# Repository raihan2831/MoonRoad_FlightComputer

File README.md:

# MoonRoad – F-Class Thrust Vector Control (TVC) Rocket

## 🚀 Overview
**MoonRoad** is an ambitious student-led rocketry project focused on developing an F-class Thrust Vector Control (TVC) rocket. Grounded in the core mission of **VITAL**, the project aims to pioneer reusable vertical take-off and landing (VTVL) rocket systems. 

Through iterative flight testing, precise mathematical modeling, and advanced navigation control, MoonRoad pushes the boundaries of student-engineered aerospace technology.

---

## 🌍 Mission & Vision

### 1. Technical Focus
* **Vertical Take-off & Landing (VTVL):** Designing systems capable of multiple take-offs and landings using rocket motors to refine flight hardware and control loops.
* **Thrust Vector Control & Navigation:** Developing robust dynamic models, state-space equations, and cascade PID control algorithms to manage real-time stabilization and trajectory tracking.
* **Modular Avionics Architecture:** Integrating custom-built Power Distribution Boards (PDBs), high-precision flight computers, high-voltage servos (BMS-A10H), and onboard sensor suites (IMU, barometer, LoRa telemetry).

### 2. Social & Environmental Focus (Sustainability)
* **Reusability over Disposable Hardware:** Challenging the traditional single-use paradigm of model and amateur rocketry to promote sustainable engineering practices.
* **Space Debris Mitigation:** Addressing the critical global challenge of orbital debris and dead satellites that endanger future human spaceflight and near-Earth operations.
* **Interplanetary Readiness:** Aligning with the sustainable technologies required for future long-duration exploration and landing missions on Mars.

---

## 📂 Repository Structure

- **`Power Delivery Board/`** – KiCad schematics, PCB layouts, and component BOMs for the custom power distribution and management system.
- **`Flight Computer PCB/`** – KiCad project files and gerbers for the main flight computer and sensor integration board.
- **`Firmware/`** – Embedded C/C++ firmware (PlatformIO) running on microcontrollers for sensor fusion, telemetry, and actuator control.
- **`Simulation Control/`** – MATLAB and Simulink models implementing state-space representations and cascade PID tuning for the TVC testbench.
- **`telemetry Analysis/`** – Python scripts (NumPy, Matplotlib) for post-flight data processing, sensor logging analysis, and trajectory evaluation.

---

## 🤝 Contributing & Teamwork
MoonRoad brings together diverse engineering disciplines—spanning embedded systems, PCB design, control theory, and mechanical packaging. Whether you are working on hardware integration or flight code, every subsystem is built with flight-readiness and reusability in mind.

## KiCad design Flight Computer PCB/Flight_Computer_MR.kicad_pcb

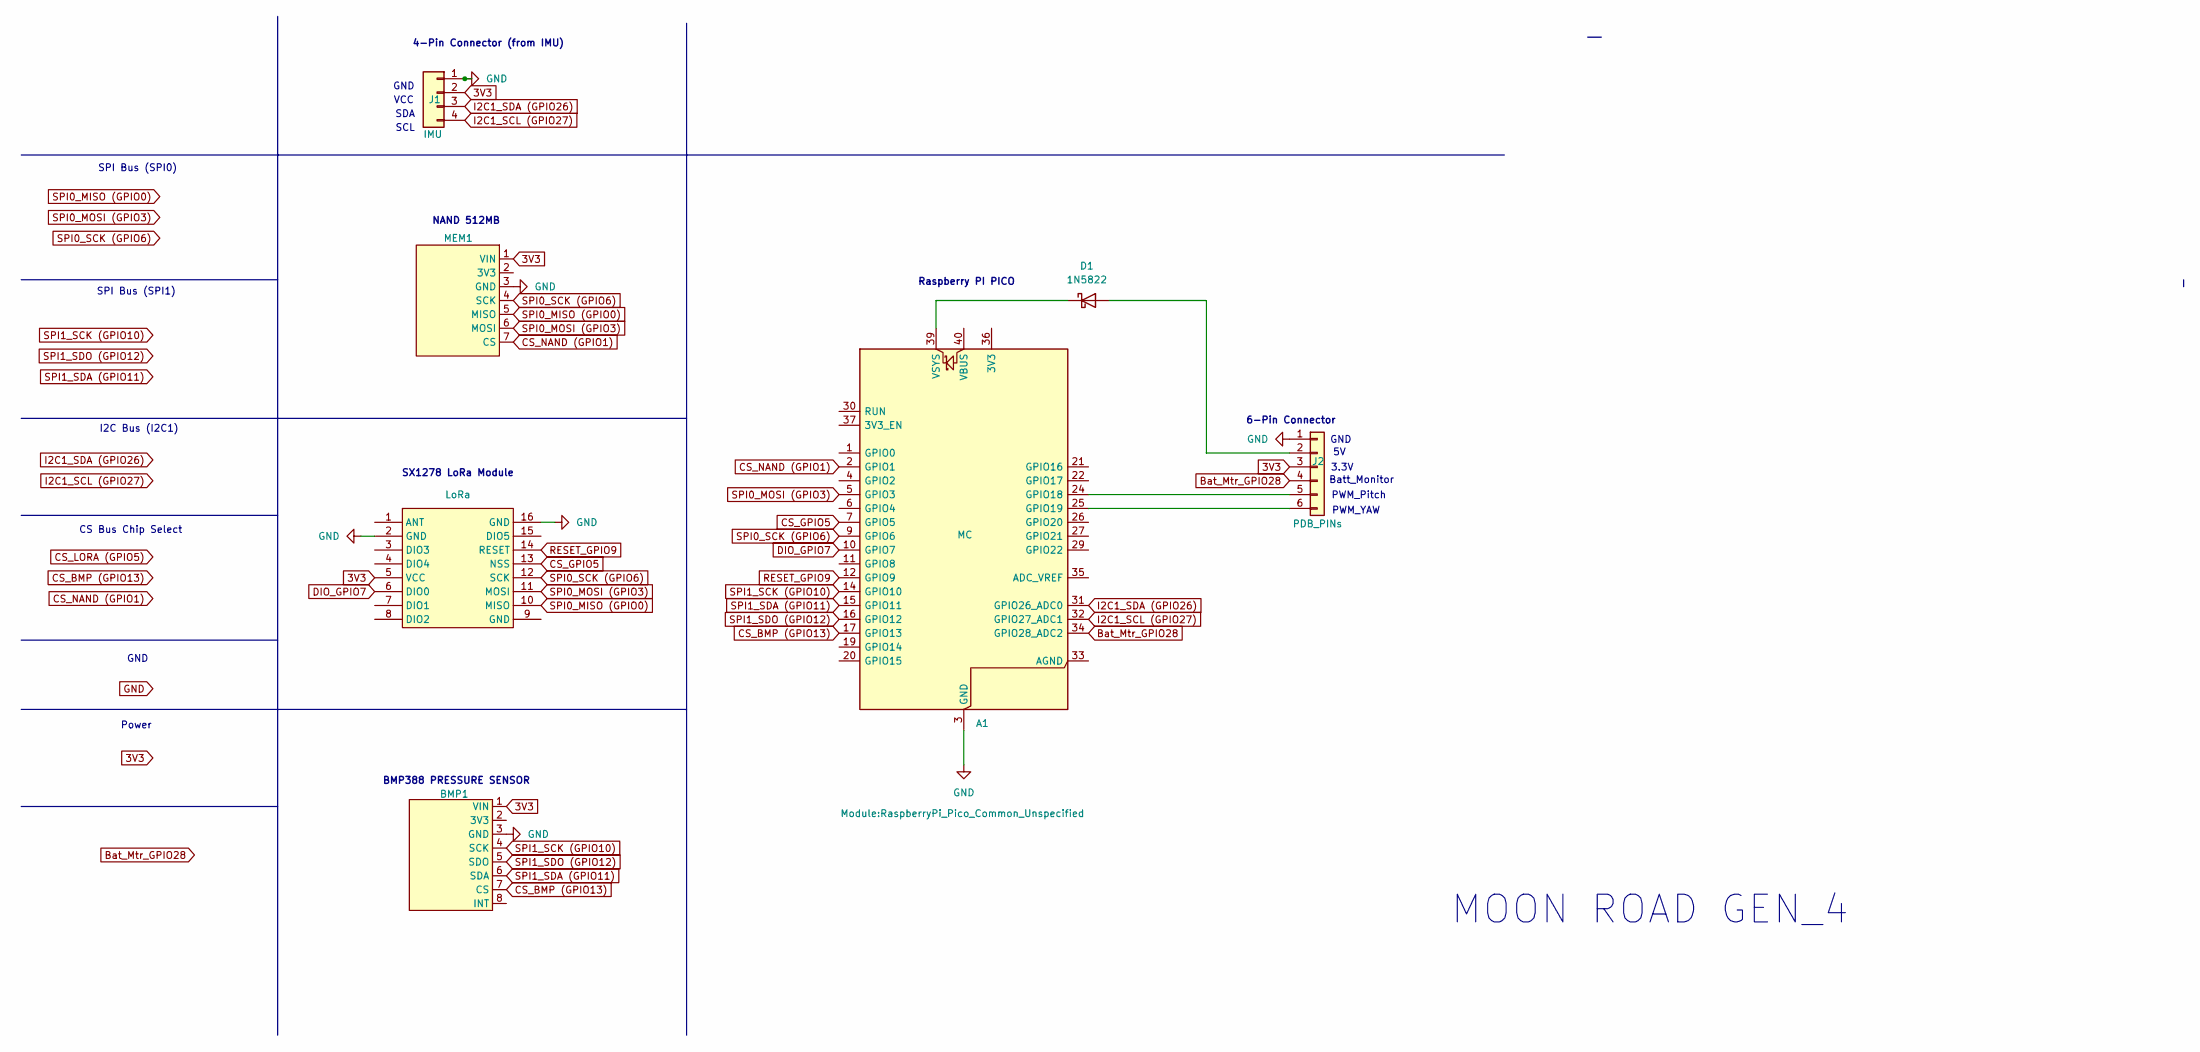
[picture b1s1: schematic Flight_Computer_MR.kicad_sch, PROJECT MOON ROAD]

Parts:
A1: MC; RaspberryPi_Pico_Common_Unspecified
BMP1: PinHeader_1x08_P2.54mm_Vertical
D1: 1N5822; D_DO-201AD_P15.24mm_Horizontal
J1: IMU; NS-Tech_Grove_1x04_P2mm_Vertical
J2: PDB_PINs; PinHeader_1x06_P2.54mm_Vertical
MEM1: PinHeader_1x07_P2.54mm_Vertical
RFS1: LoRa; RFSTX1278

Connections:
3V3: BMP1.1 (VIN), J1.2 (VCC), J2.3 (3V3), MEM1.1 (VIN), RFS1.5 (VCC)
Bat_Mtr_GPIO28: A1.34 (GPIO28_ADC2), J2.4 (Batt_Monitor)
CS_BMP (GPIO13): A1.17 (GPIO13), BMP1.7 (CS)
CS_GPIO5: A1.7 (GPIO5), RFS1.13 (NSS)
CS_NAND (GPIO1): A1.2 (GPIO1), MEM1.7 (CS)
DIO_GPIO7: A1.10 (GPIO7), RFS1.6 (DIO0)
GND: A1.3 (GND), A1.8 (GND), A1.13 (GND), A1.18 (GND), A1.23 (GND), A1.28 (GND), A1.38 (GND), BMP1.3 (GND), J1.1 (GND), J2.1 (GND), MEM1.3 (GND), RFS1.2 (GND), RFS1.16 (GND)
I2C1_SCL (GPIO27): A1.32 (GPIO27_ADC1), J1.4 (SCL)
I2C1_SDA (GPIO26): A1.31 (GPIO26_ADC0), J1.3 (SDA)
unnamed: A1.24 (GPIO18), J2.5 (PWM_Pitch)
unnamed: A1.25 (GPIO19), J2.6 (PWM_Yaw)
unnamed: A1.39 (VSYS), D1.1 (K)
unnamed: D1.2 (A), J2.2 (5V)
RESET_GPIO9: A1.12 (GPIO9), RFS1.14 (RESET)
SPI0_MISO (GPIO0): MEM1.5 (MISO), RFS1.10 (MISO)
SPI0_MOSI (GPIO3): A1.5 (GPIO3), MEM1.6 (MOSI), RFS1.11 (MOSI)
SPI0_SCK (GPIO6): A1.9 (GPIO6), MEM1.4 (SCK), RFS1.12 (SCK)
SPI1_SCK (GPIO10): A1.14 (GPIO10), BMP1.4 (SCK)
SPI1_SDA (GPIO11): A1.15 (GPIO11), BMP1.6 (SDA)
SPI1_SDO (GPIO12): A1.16 (GPIO12), BMP1.5 (SDO)

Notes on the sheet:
NAND 512MB
SX1278 LoRa Module
GND
SPI Bus (SPI0)
SCL
3.3V
6-Pin Connector
PWM_Pitch
SDA
Batt_Monitor
BMP388 PRESSURE SENSOR
Power
SPI Bus (SPI1)
CS Bus Chip Select
PWM_YAW
MOON ROAD GEN_4
I2C Bus (I2C1)
VCC
4-Pin Connector (from IMU)
Raspberry PI PICO
GND

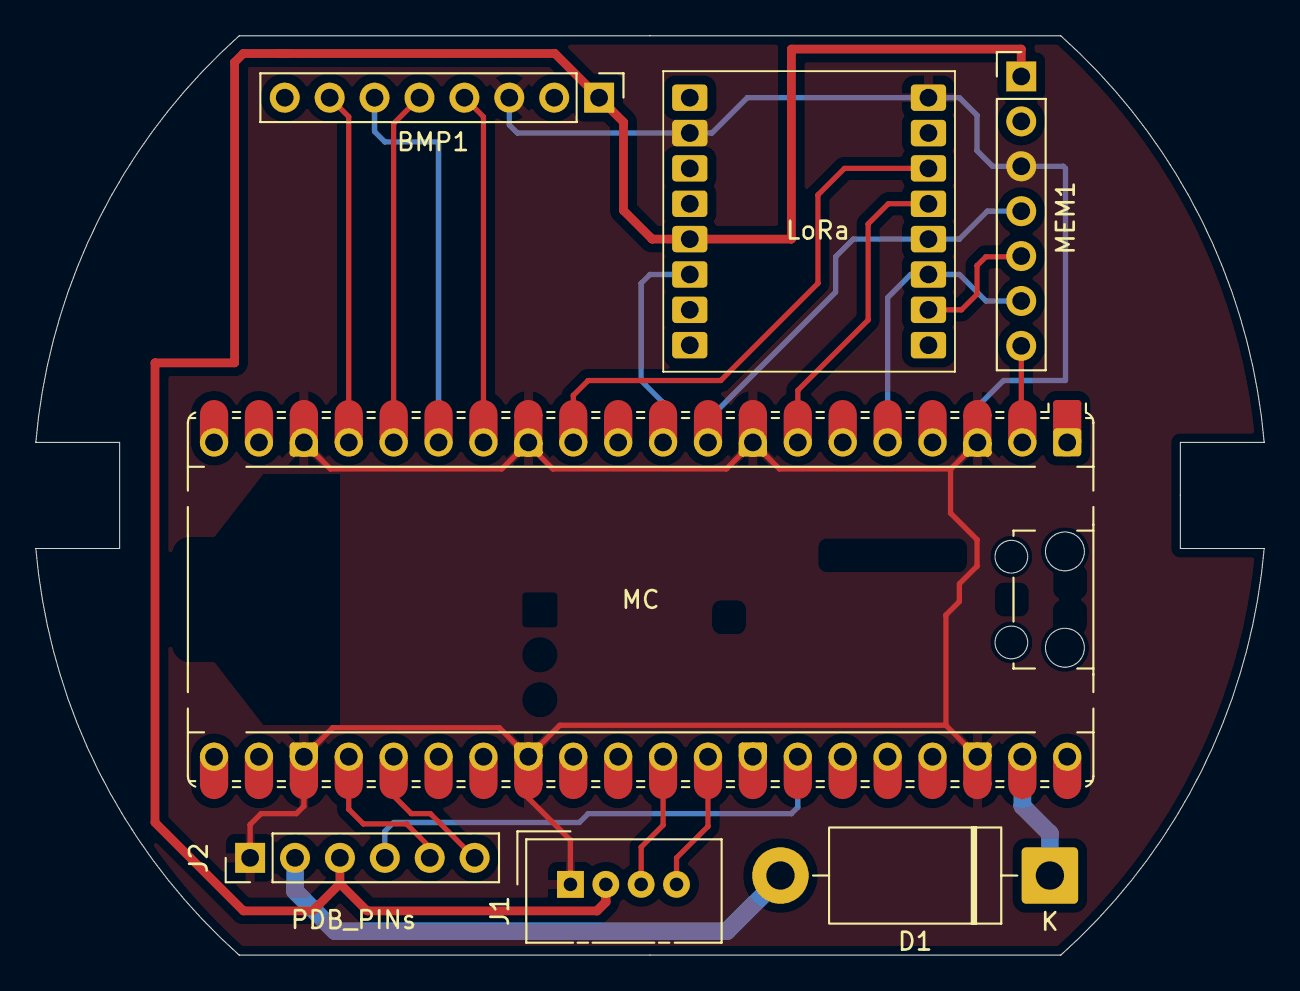
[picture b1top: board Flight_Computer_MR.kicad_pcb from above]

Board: 2 copper layers, 69.5 x 52.0 mm, 7 parts (0 on the bottom side), 20 nets.

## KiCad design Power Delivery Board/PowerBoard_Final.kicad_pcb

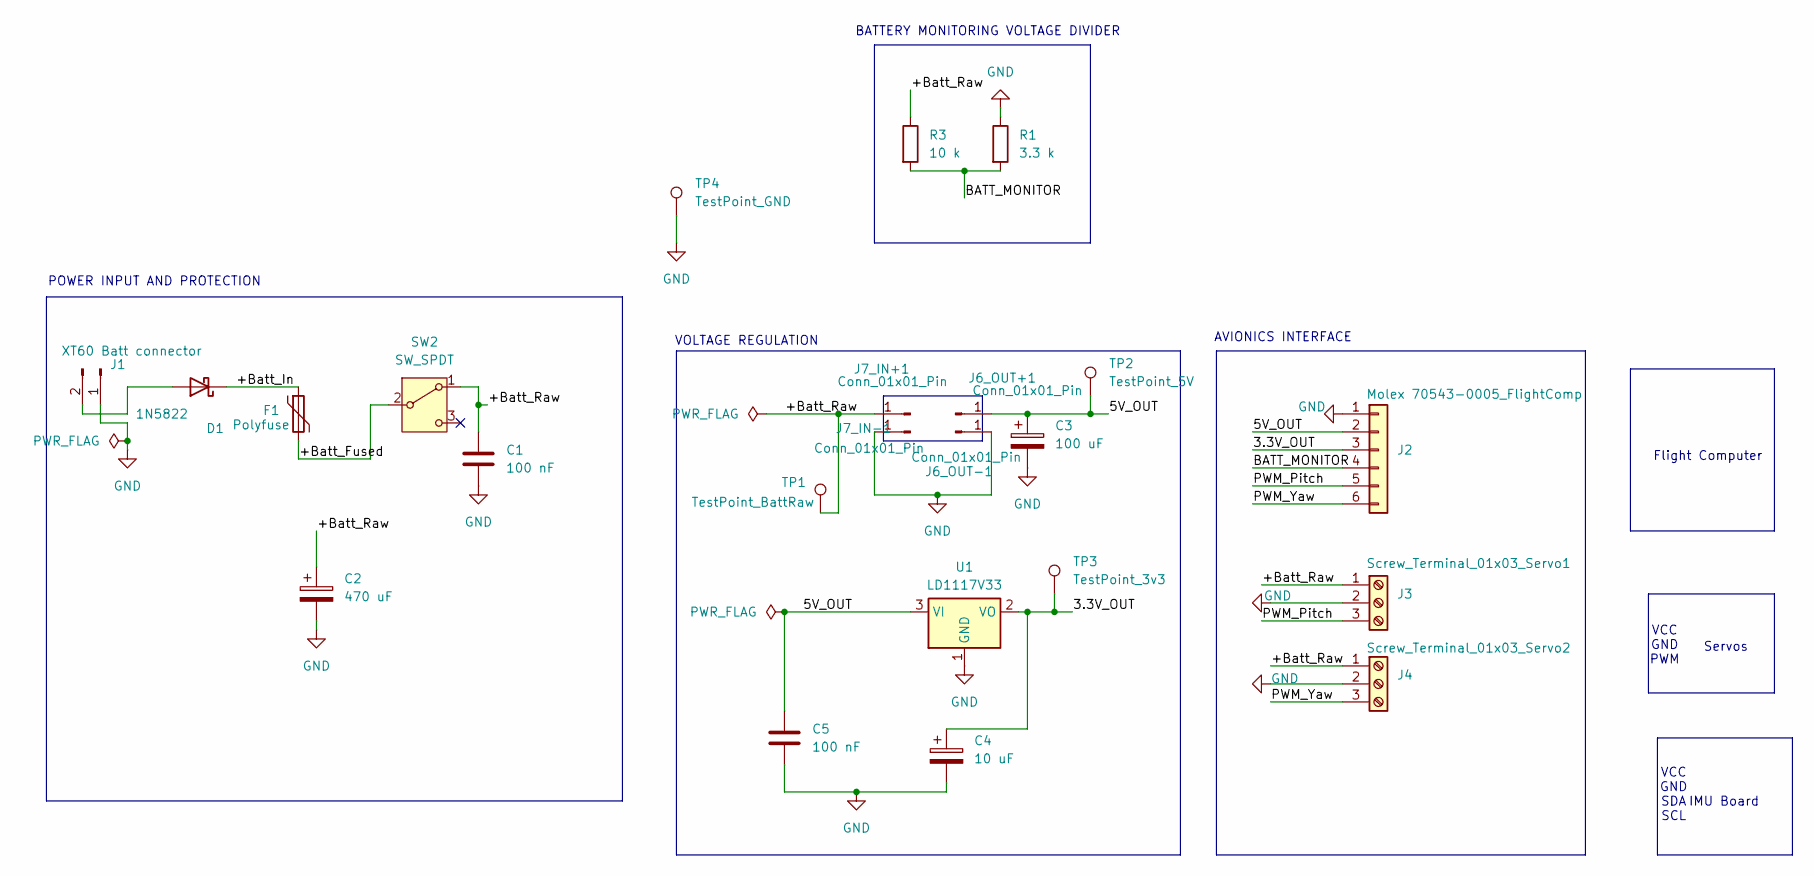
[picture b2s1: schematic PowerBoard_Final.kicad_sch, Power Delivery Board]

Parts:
C1, C5: 100 nF; C_Disc_D5.0mm_W2.5mm_P5.00mm
C2: 470 uF; CP_Radial_D5.0mm_P2.00mm
C3: 100 uF; CP_Radial_D5.0mm_P2.00mm
C4: 10 uF; CP_Radial_D5.0mm_P2.00mm
D1: 1N5822; D_DO-201AD_P15.24mm_Horizontal
F1: Polyfuse; C_Disc_D12.5mm_W5.0mm_P7.50mm
J1: XT60 Batt connector; AMASS_XT30U-F_1x02_P5.0mm_Vertical
J2: Molex 70543-0005_FlightComp; Molex_SL_171971-0006_1x06_P2.54mm_Vertical
J3: Screw_Terminal_01x03_Servo1; TerminalBlock_Phoenix_MKDS-1,5-3_1x03_P5.00mm_Horizontal
J4: Screw_Terminal_01x03_Servo2; TerminalBlock_Phoenix_MKDS-1,5-3_1x03_P5.00mm_Horizontal
J6_OUT+1, J6_OUT-1, J7_IN+1, J7_IN-1: Conn_01x01_Pin; PinHeader_1x01_P2.54mm_Vertical
R1: 3.3 k; R_Axial_DIN0204_L3.6mm_D1.6mm_P7.62mm_Horizontal
R3: 10 k; R_Axial_DIN0204_L3.6mm_D1.6mm_P7.62mm_Horizontal
SW2: SW_SPDT; SW_Slide-03_Wuerth-WS-SLTV_10x2.5x6.4_P2.54mm
TP1: TestPoint_BattRaw; TestPoint_Pad_D1.0mm
TP2: TestPoint_5V; TestPoint_Pad_D1.0mm
TP3: TestPoint_3v3; TestPoint_Pad_D1.0mm
TP4: TestPoint_GND; TestPoint_Pad_D1.0mm
U1: LD1117V33; TO-220-3_Vertical

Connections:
/3.3V_OUT: C4.1, J2.3, TP3.1, U1.2 (VO)
/5V_OUT: C3.1, C5.1, J2.2, J6_OUT+1.1, TP2.1, U1.3 (VI)
/+Batt_Fused: F1.2, SW2.2 (B)
/+Batt_In: D1.1 (K), F1.1
/+Batt_Raw: C1.2, C2.1, J3.1, J4.1, J7_IN+1.1, R3.1, SW2.1 (A), TP1.1
/BATT_MONITOR: J2.4, R1.2, R3.2
/PWM_Pitch: J2.5, J3.3
/PWM_Yaw: J2.6, J4.3
GND: C1.1, C2.2, C3.2, C4.2, C5.2, J1.1, J2.1, J3.2, J4.2, J6_OUT-1.1, J7_IN-1.1, R1.1, TP4.1, U1.1 (GND)
unnamed: D1.2 (A), J1.2

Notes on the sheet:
VCC GND PWM
POWER INPUT AND PROTECTION
Flight Computer
VOLTAGE REGULATION
AVIONICS INTERFACE
BATTERY MONITORING VOLTAGE DIVIDER
IMU Board
VCC GND SDA SCL
Servos

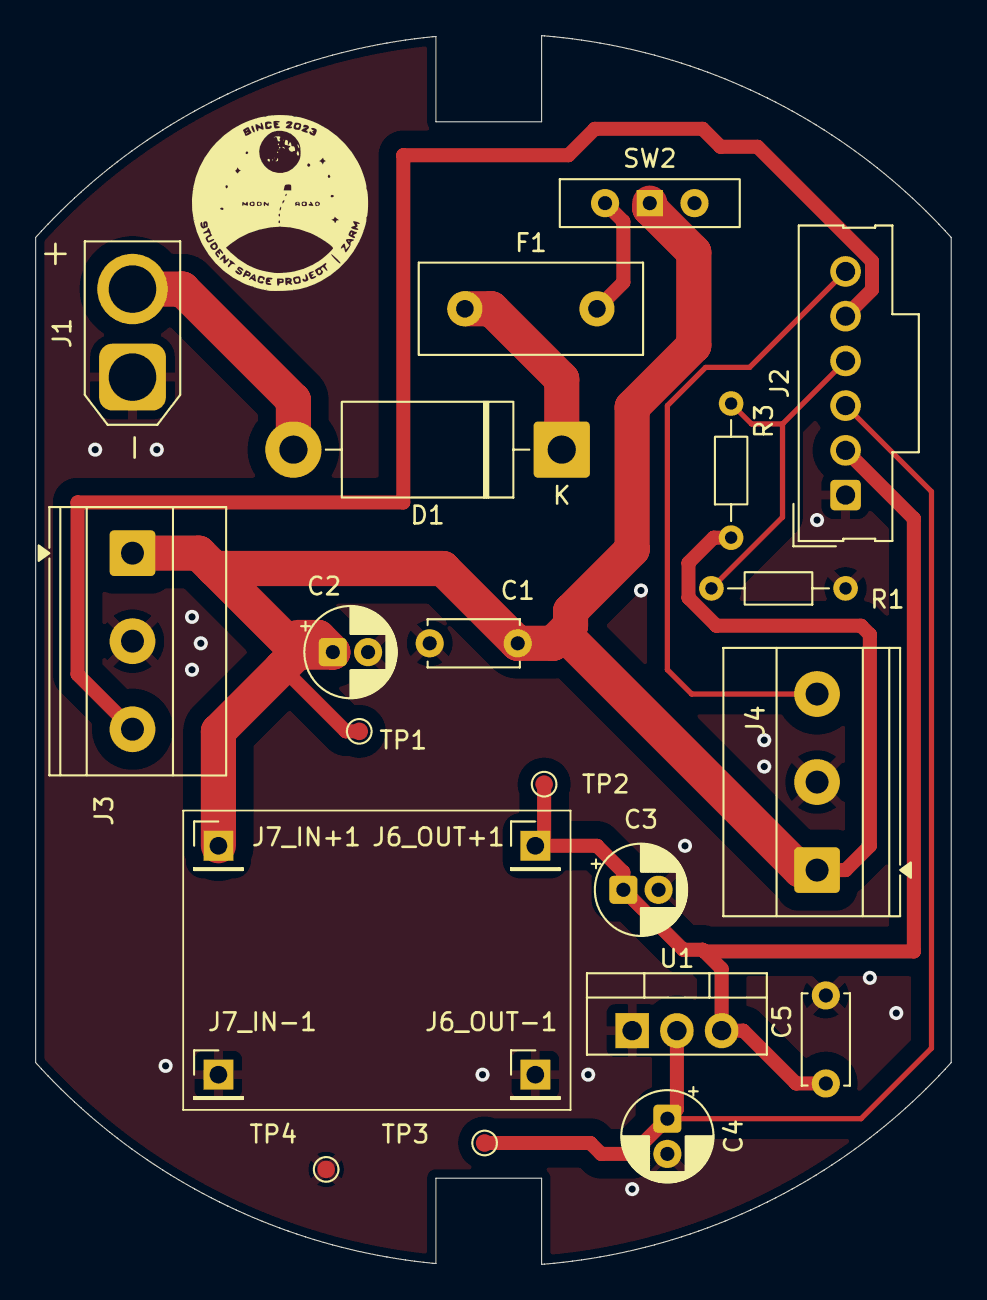
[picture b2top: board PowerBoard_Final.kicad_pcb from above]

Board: 2 copper layers, 52.0 x 69.8 mm, 23 parts (0 on the bottom side), 10 nets.
